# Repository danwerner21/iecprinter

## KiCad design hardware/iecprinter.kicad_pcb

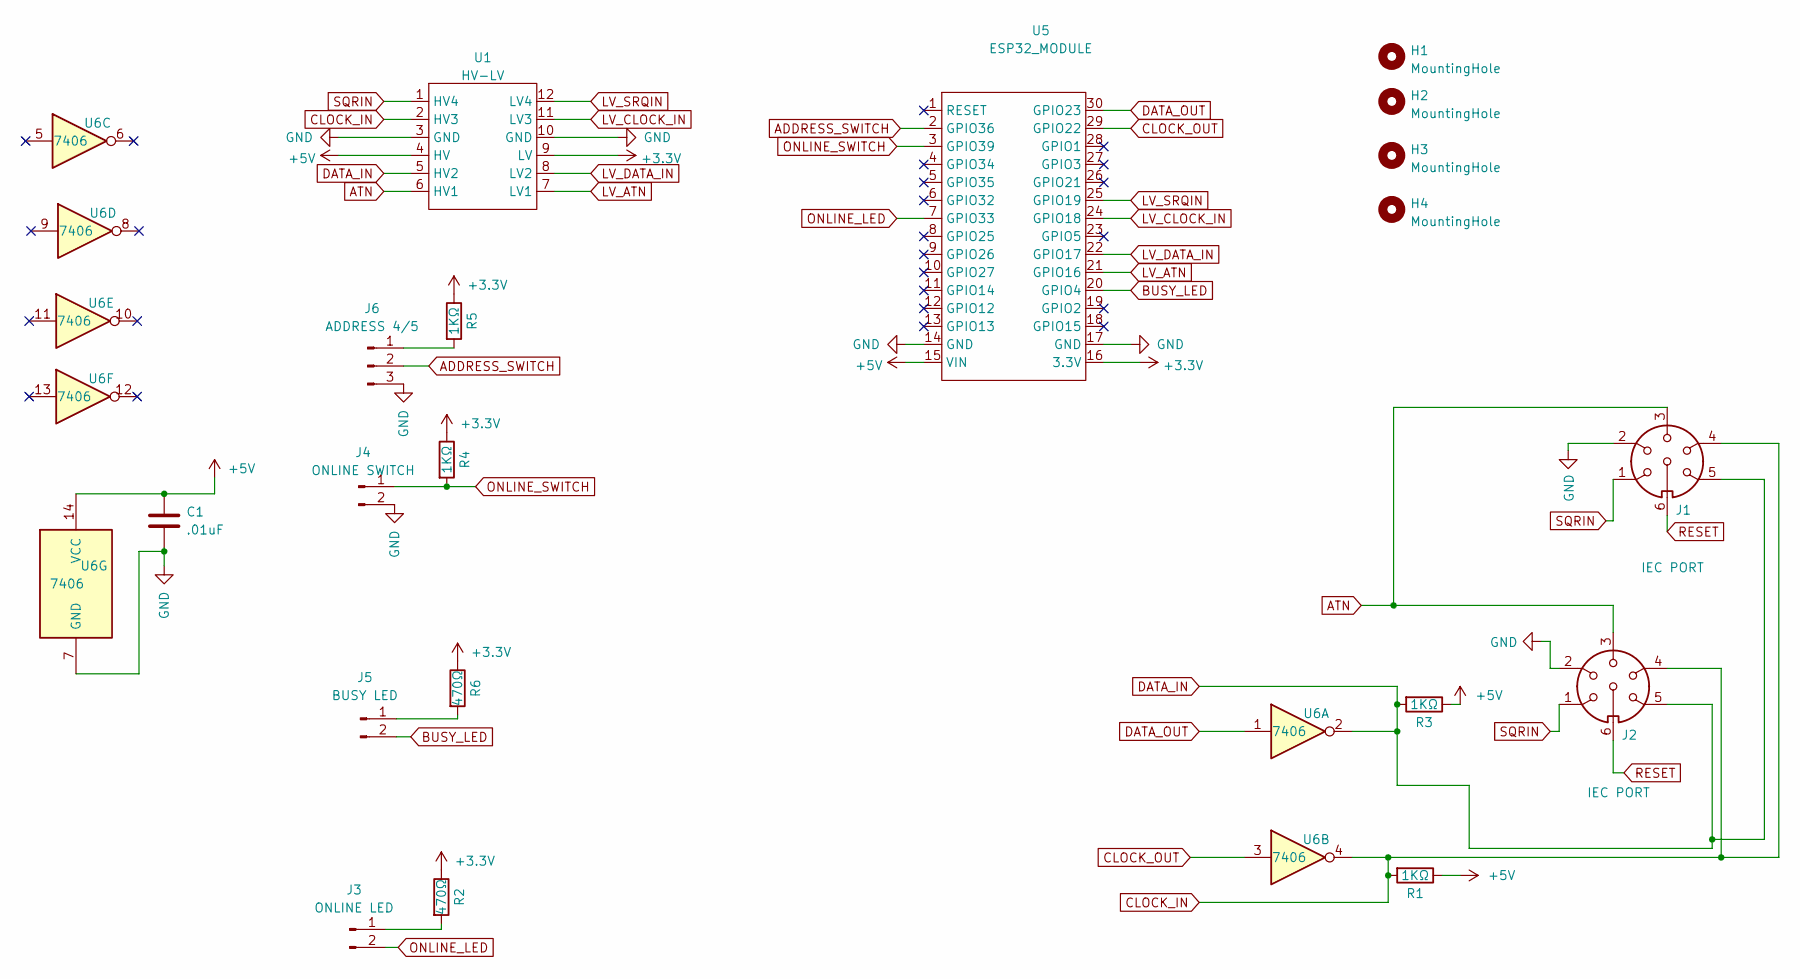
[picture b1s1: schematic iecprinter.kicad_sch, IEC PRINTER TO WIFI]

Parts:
C1: .01uF; C_Disc_D5.0mm_W2.5mm_P5.00mm
H1, H2, H3, H4: MountingHole; MountingHole_3.2mm_M3
J1, J2: IEC PORT; din6
J3: ONLINE LED; PinHeader_1x02_P2.54mm_Vertical
J4: ONLINE SWITCH; PinHeader_1x02_P2.54mm_Vertical
J5: BUSY LED; PinHeader_1x02_P2.54mm_Vertical
J6: ADDRESS 4/5; PinHeader_1x03_P2.54mm_Vertical
R1, R3, R4, R5: 1KΩ; R_Axial_DIN0204_L3.6mm_D1.6mm_P5.08mm_Horizontal
R2, R6: 470Ω; R_Axial_DIN0204_L3.6mm_D1.6mm_P5.08mm_Horizontal
U1: HV-LV
U5: ESP32_MODULE; ESP32_DEVKIT_30
U6: 7406; DIP-14_W7.62mm_Socket

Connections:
+3.3V: R2.1, R4.1, R5.1, R6.1, U1.9 (LV), U5.16 (3.3V)
+5V: C1.1, R1.1, R3.1, U1.4 (HV), U5.15 (VIN), U6.14 (VCC)
ADDRESS_SWITCH: J6.2, U5.2 (GPIO36)
ATN: J1.3, J2.3, U1.6 (HV1)
BUSY_LED: J5.2, U5.20 (GPIO4)
CLOCK_IN: J1.4, J2.4, R1.2, U1.2 (HV3), U6.4
CLOCK_OUT: U5.29 (GPIO22), U6.3
DATA_IN: J1.5, J2.5, R3.2, U1.5 (HV2), U6.2
DATA_OUT: U5.30 (GPIO23), U6.1
GND: C1.2, J1.2, J2.2, J4.2, J6.3, U1.3 (GND), U1.10 (GND), U5.14 (GND), U5.17 (GND), U6.7 (GND)
LV_ATN: U1.7 (LV1), U5.21 (GPIO16)
LV_CLOCK_IN: U1.11 (LV3), U5.24 (GPIO18)
LV_DATA_IN: U1.8 (LV2), U5.22 (GPIO17)
LV_SRQIN: U1.12 (LV4), U5.25 (GPIO19)
unnamed: J3.1, R2.2
unnamed: J5.1, R6.2
unnamed: J6.1, R5.2
ONLINE_LED: J3.2, U5.7 (GPIO33)
ONLINE_SWITCH: J4.1, R4.2, U5.3 (GPIO39)
RESET: J1.6, J2.6
SQRIN: J1.1, J2.1, U1.1 (HV4)

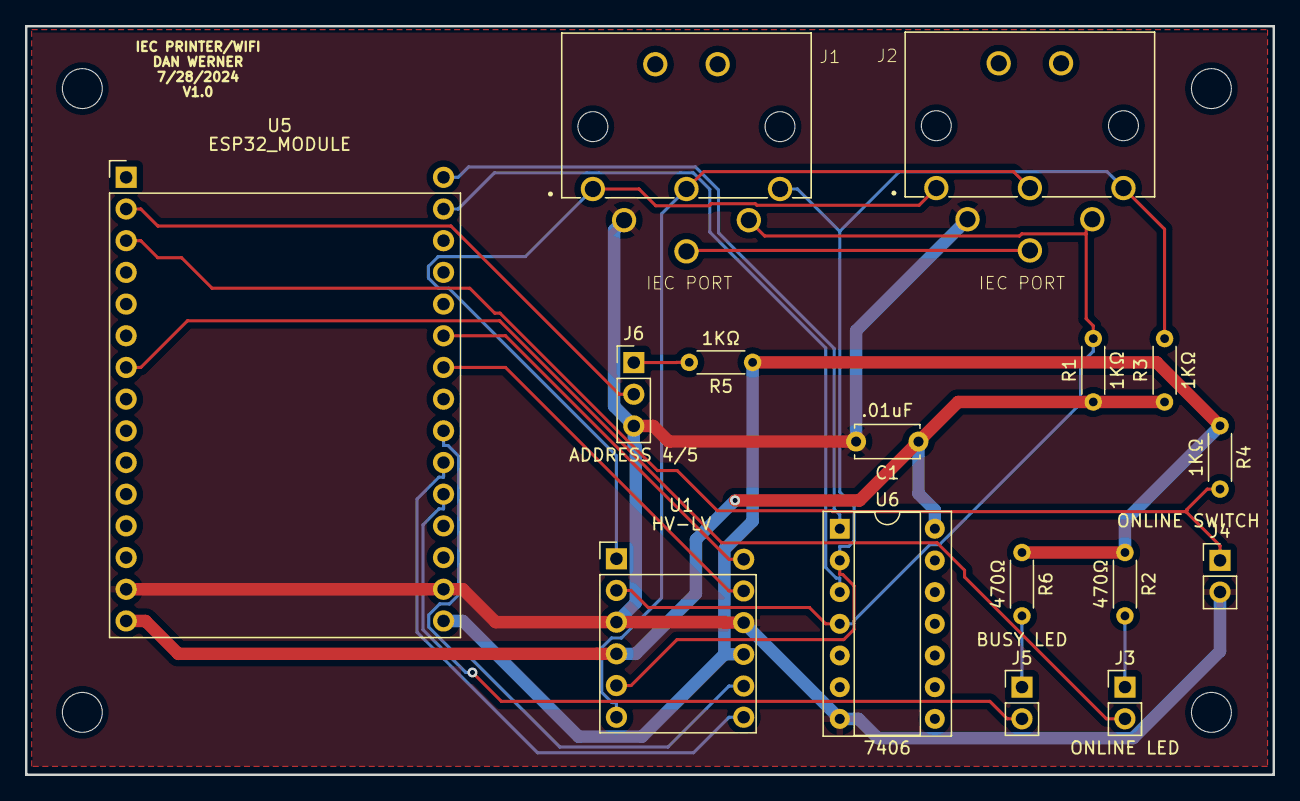
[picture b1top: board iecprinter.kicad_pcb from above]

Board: 2 copper layers, 100.0 x 60.0 mm, 20 parts (0 on the bottom side), 21 nets.

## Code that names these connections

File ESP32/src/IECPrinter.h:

#include "IECDevice.h"
#include "iecwifi.h"

#define BUSY_LED   2
#define ONLINE_LED 33

// IEC Serial Connections
#define PIN_ATN   16
#define PIN_DATA  17
#define PIN_CLK   18
#define PIN_RESET 25
//
// DATA - X       X - SRQ
//    RESET - X
//  CLK - X       X - GND
//            X - ATN
//



class IECPrinter : public IECDevice
{
 public:
  IECPrinter() : IECDevice(PIN_ATN, PIN_CLK, PIN_DATA) {}
  iecWifi espWifi;
  virtual int8_t canRead();
  virtual byte   read();

  virtual int8_t canWrite();
  virtual void   write(byte data);
  virtual void  setStatus(bool status);

 private:
  bool online;
};

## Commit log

2024-07-28 initial
